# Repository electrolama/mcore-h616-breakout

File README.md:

# mcore-h616-breakout

A breakout for the [Mango Pi MCore-H616](https://mangopi.org/mcoreh616) module.

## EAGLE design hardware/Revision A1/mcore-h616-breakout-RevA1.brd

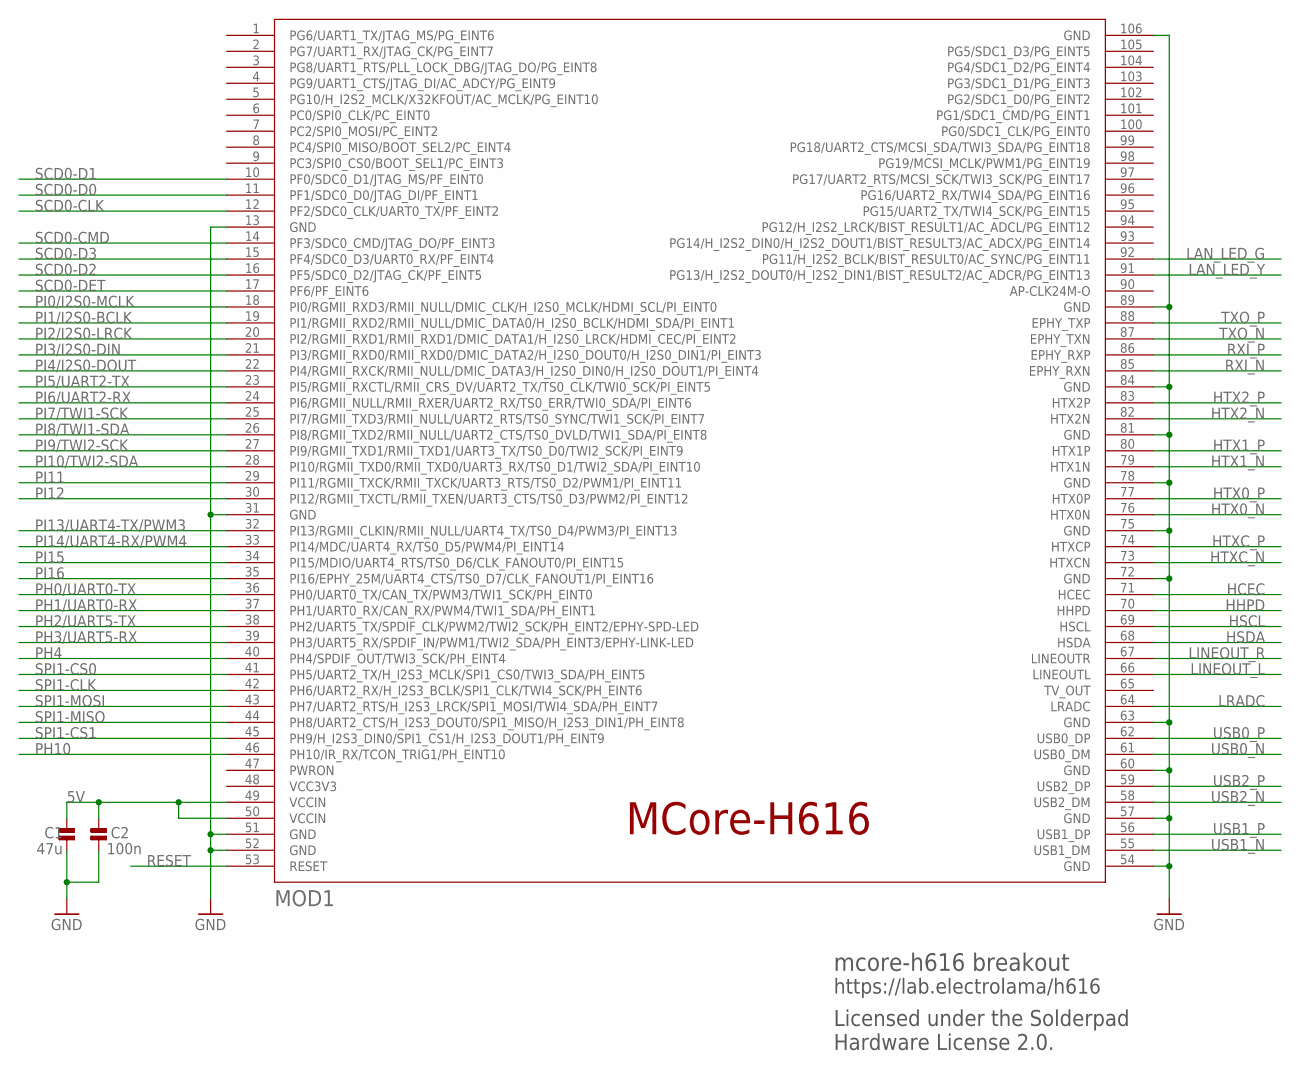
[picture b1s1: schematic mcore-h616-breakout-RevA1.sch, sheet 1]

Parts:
C1: 47u; _PKG_C_1206; JLCASSY C96123
C2: 100n; _PKG_C_0402; JLCASSY C307331
MOD1: WIDORA_MCORE-H616_V1; MCORE-H616_V1

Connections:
5V: C1.2, C2.2, MOD1.49 (VCCIN), MOD1.50 (VCCIN); also elsewhere on the board
GND: C1.1, C2.1, MOD1.13 (GND), MOD1.31 (GND), MOD1.51 (GND), MOD1.52 (GND), MOD1.54 (GND), MOD1.57 (GND), MOD1.60 (GND), MOD1.63 (GND), MOD1.72 (GND), MOD1.75 (GND), MOD1.78 (GND), MOD1.81 (GND), MOD1.84 (GND), MOD1.89 (GND), MOD1.106 (GND); also elsewhere on the board
HCEC: MOD1.71 (HCEC); also elsewhere on the board
HHPD: MOD1.70 (HHPD); also elsewhere on the board
HSCL: MOD1.69 (HSCL); also elsewhere on the board
HSDA: MOD1.68 (HSDA); also elsewhere on the board
HTX0_N: MOD1.76 (HTX0N); also elsewhere on the board
HTX0_P: MOD1.77 (HTX0P); also elsewhere on the board
HTX1_N: MOD1.79 (HTX1N); also elsewhere on the board
HTX1_P: MOD1.80 (HTX1P); also elsewhere on the board
HTX2_N: MOD1.82 (HTX2N); also elsewhere on the board
HTX2_P: MOD1.83 (HTX2P); also elsewhere on the board
HTXC_N: MOD1.73 (HTXCN); also elsewhere on the board
HTXC_P: MOD1.74 (HTXCP); also elsewhere on the board
LAN_LED_G: MOD1.92 (PG11/H_I2S2_BCLK/BIST_RESULT0/AC_SYNC/P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); also elsewhere on the board
LAN_LED_Y: MOD1.91 (PG13/H_I2S2_DOUT0/H_I2S2_DIN1/BIST_RESU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); also elsewhere on the board
LINEOUT_L: MOD1.66 (LINEOUTL); also elsewhere on the board
LINEOUT_R: MOD1.67 (LINEOUTR); also elsewhere on the board
LRADC: MOD1.64 (LRADC); also elsewhere on the board
PH0/UART0-TX: MOD1.36 (PH0/UART0_TX/CAN_TX/PWM3/TWI1_SCK/PH_EI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); also elsewhere on the board
PH1/UART0-RX: MOD1.37 (PH1/UART0_RX/CAN_RX/PWM4/TWI1_SDA/PH_EI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); also elsewhere on the board
PH2/UART5-TX: MOD1.38 (PH2/UART5_TX/SPDIF_CLK/PWM2/TWI2_SCK/PH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); also elsewhere on the board
PH3/UART5-RX: MOD1.39 (PH3/UART5_RX/SPDIF_IN/PWM1/TWI2_SDA/PH_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); also elsewhere on the board
PH4: MOD1.40 (PH4/SPDIF_OUT/TWI3_SCK/PH_EINT4); also elsewhere on the board
PH10: MOD1.46 (PH10/IR_RX/TCON_TRIG1/PH_EINT10); also elsewhere on the board
PI0/I2S0-MCLK: MOD1.18 (PI0/RGMII_RXD3/RMII_NULL/DMIC_CLK/H_I2S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); also elsewhere on the board
PI1/I2S0-BCLK: MOD1.19 (PI1/RGMII_RXD2/RMII_NULL/DMIC_DATA0/H_I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); also elsewhere on the board
PI2/I2S0-LRCK: MOD1.20 (PI2/RGMII_RXD1/RMII_RXD1/DMIC_DATA1/H_I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); also elsewhere on the board
PI3/I2S0-DIN: MOD1.21 (PI3/RGMII_RXD0/RMII_RXD0/DMIC_DATA2/H_I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); also elsewhere on the board
PI4/I2S0-DOUT: MOD1.22 (PI4/RGMII_RXCK/RMII_NULL/DMIC_DATA3/H_I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); also elsewhere on the board
PI5/UART2-TX: MOD1.23 (PI5/RGMII_RXCTL/RMII_CRS_DV/UART2_TX/TS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); also elsewhere on the board
PI6/UART2-RX: MOD1.24 (PI6/RGMII_NULL/RMII_RXER/UART2_RX/TS0_E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); also elsewhere on the board
PI7/TWI1-SCK: MOD1.25 (PI7/RGMII_TXD3/RMII_NULL/UART2_RTS/TS0_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); also elsewhere on the board
PI8/TWI1-SDA: MOD1.26 (PI8/RGMII_TXD2/RMII_NULL/UART2_CTS/TS0_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); also elsewhere on the board
PI9/TWI2-SCK: MOD1.27 (PI9/RGMII_TXD1/RMII_TXD1/UART3_TX/TS0_D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); also elsewhere on the board
PI10/TWI2-SDA: MOD1.28 (PI10/RGMII_TXD0/RMII_TXD0/UART3_RX/TS0_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); also elsewhere on the board
PI11: MOD1.29 (PI11/RGMII_TXCK/RMII_TXCK/UART3_RTS/TS0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); also elsewhere on the board
PI12: MOD1.30 (PI12/RGMII_TXCTL/RMII_TXEN/UART3_CTS/TS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); also elsewhere on the board
PI13/UART4-TX/PWM3: MOD1.32 (PI13/RGMII_CLKIN/RMII_NULL/UART4_TX/TS0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); also elsewhere on the board
PI14/UART4-RX/PWM4: MOD1.33 (PI14/MDC/UART4_RX/TS0_D5/PWM4/PI_EINT14); also elsewhere on the board
PI15: MOD1.34 (PI15/MDIO/UART4_RTS/TS0_D6/CLK_FANOUT0/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); also elsewhere on the board
PI16: MOD1.35 (PI16/EPHY_25M/UART4_CTS/TS0_D7/CLK_FANO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); also elsewhere on the board
RESET: MOD1.53 (RESET); also elsewhere on the board
RXI_N: MOD1.85 (EPHY_RXN); also elsewhere on the board
RXI_P: MOD1.86 (EPHY_RXP); also elsewhere on the board
SCD0-CLK: MOD1.12 (PF2/SDC0_CLK/UART0_TX/PF_EINT2); also elsewhere on the board
SCD0-CMD: MOD1.14 (PF3/SDC0_CMD/JTAG_DO/PF_EINT3); also elsewhere on the board
SCD0-D0: MOD1.11 (PF1/SDC0_D0/JTAG_DI/PF_EINT1); also elsewhere on the board
SCD0-D1: MOD1.10 (PF0/SDC0_D1/JTAG_MS/PF_EINT0); also elsewhere on the board
SCD0-D2: MOD1.16 (PF5/SDC0_D2/JTAG_CK/PF_EINT5); also elsewhere on the board
SCD0-D3: MOD1.15 (PF4/SDC0_D3/UART0_RX/PF_EINT4); also elsewhere on the board
SCD0-DET: MOD1.17 (PF6/PF_EINT6); also elsewhere on the board
SPI1-CLK: MOD1.42 (PH6/UART2_RX/H_I2S3_BCLK/SPI1_CLK/TWI4_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); also elsewhere on the board
SPI1-CS0: MOD1.41 (PH5/UART2_TX/H_I2S3_MCLK/SPI1_CS0/TWI3_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); also elsewhere on the board
SPI1-CS1: MOD1.45 (PH9/H_I2S3_DIN0/SPI1_CS1/H_I2S3_DOUT1/P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); also elsewhere on the board
SPI1-MISO: MOD1.44 (PH8/UART2_CTS/H_I2S3_DOUT0/SPI1_MISO/H_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); also elsewhere on the board
SPI1-MOSI: MOD1.43 (PH7/UART2_RTS/H_I2S3_LRCK/SPI1_MOSI/TWI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); also elsewhere on the board
TXO_N: MOD1.87 (EPHY_TXN); also elsewhere on the board
TXO_P: MOD1.88 (EPHY_TXP); also elsewhere on the board
USB0_N: MOD1.61 (USB0_DM); also elsewhere on the board
USB0_P: MOD1.62 (USB0_DP); also elsewhere on the board
USB1_N: MOD1.55 (USB1_DM); also elsewhere on the board
USB1_P: MOD1.56 (USB1_DP); also elsewhere on the board
USB2_N: MOD1.58 (USB2_DM); also elsewhere on the board
USB2_P: MOD1.59 (USB2_DP); also elsewhere on the board

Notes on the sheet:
mcore-h616 breakout
https://lab.electrolama/h616
Licensed under the Solderpad Hardware License 2.0.

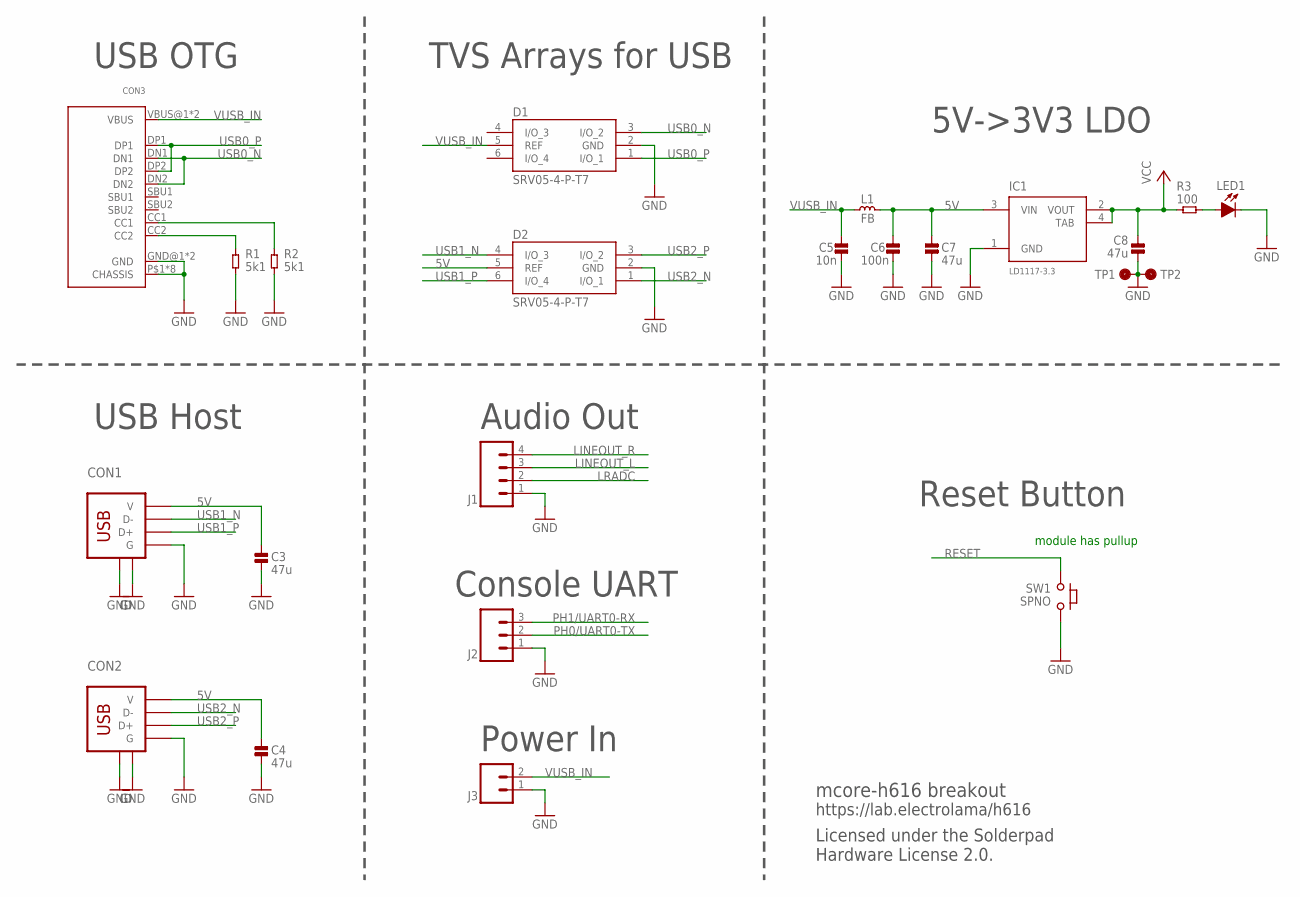
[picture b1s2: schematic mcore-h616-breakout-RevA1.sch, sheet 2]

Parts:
C3, C4, C7, C8: 47u; _PKG_C_1206; JLCASSY C96123
C5: 10n; _PKG_C_0402; JLCASSY C15195
C6: 100n; _PKG_C_0402; JLCASSY C307331
CON1, CON2: USB-A-FEMALE-JING-912-121A2023S10100; JING_912-121A2023S10100; JLCASSY C42428
CON3: USBC_USB-C-12; USBC_C-31-M-12; JLCASSY C165948
D1, D2: SRV05-4-P-T7; SOT95P280X145-6N; JLCASSY C85364
IC1: LD1117-3.3; _PKG_SOT223-4_TI-DCY4; JLCASSY C6186
J1: CONN_04LOCK; 1X04_LOCK
J2: CONN_03LOCK; 1X03_LOCK
J3: CONN_02LOCK; 1X02_LOCK
L1: FB; _PKG_C_0805; JLCASSY C75661
LED1: LED-0805; _PKG_LED_0805; JLCASSY C2296
R1, R2: 5k1; _PKG_R_0402; JLCASSY C25905
R3: 100; _PKG_R_0402; JLCASSY C25076
SW1: SPNO; GENERIC_SPNO_4P_6X6MM; JLCASSY C620316
TP1, TP2: TP; TP_DOT_1.5X1.5MM

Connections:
5V: C3.2, C4.2, C6.2, C7.2, CON1.VBUS (V), CON2.VBUS (V), D2.5 (REF), IC1.3 (VIN), L1.2; also elsewhere on the board
GND: C3.1, C4.1, C5.1, C6.1, C7.1, C8.1, CON1.GND (G), CON1.P$5 (SHIELD1), CON1.P$6 (SHIELD2), CON2.GND (G), CON2.P$5 (SHIELD1), CON2.P$6 (SHIELD2), CON3.GND@1 (GND), CON3.GND@2 (GND), CON3.P$1 (CHASSIS), CON3.P$2 (CHASSIS), CON3.P$3 (CHASSIS), CON3.P$4 (CHASSIS), CON3.P$5 (CHASSIS), CON3.P$6 (CHASSIS), CON3.P$7 (CHASSIS), CON3.P$8 (CHASSIS), D1.2 (GND), D2.2 (GND), IC1.1 (GND), J1.1, J2.1, J3.1, LED1.C, R1.1, R2.1, SW1.P$3 (2), SW1.P$4 (2), TP1.TP, TP2.TP; also elsewhere on the board
LINEOUT_L: J1.3; also elsewhere on the board
LINEOUT_R: J1.4; also elsewhere on the board
LRADC: J1.2; also elsewhere on the board
unnamed: LED1.A, R3.1
unnamed: CON3.CC1, R2.2
unnamed: CON3.CC2, R1.2
PH0/UART0-TX: J2.2; also elsewhere on the board
PH1/UART0-RX: J2.3; also elsewhere on the board
RESET: SW1.P$1 (1), SW1.P$2 (1); also elsewhere on the board
USB0_N: CON3.DN1, CON3.DN2, D1.3 (I/O_2); also elsewhere on the board
USB0_P: CON3.DP1, CON3.DP2, D1.1 (I/O_1); also elsewhere on the board
USB1_N: CON1.DM (D-), D2.4 (I/O_3); also elsewhere on the board
USB1_P: CON1.DP (D+), D2.6 (I/O_4); also elsewhere on the board
USB2_N: CON2.DM (D-), D2.1 (I/O_1); also elsewhere on the board
USB2_P: CON2.DP (D+), D2.3 (I/O_2); also elsewhere on the board
VCC: C8.2, IC1.2 (VOUT), IC1.4 (TAB), R3.2; also elsewhere on the board
VUSB_IN: C5.2, CON3.VBUS@1 (VBUS), CON3.VBUS@2 (VBUS), D1.5 (REF), J3.2, L1.1

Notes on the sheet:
module has pullup
USB OTG
TVS Arrays for USB
USB Host
Audio Out
Console UART
Power In
Reset Button
5V->3V3 LDO
mcore-h616 breakout
https://lab.electrolama/h616
Licensed under the Solderpad Hardware License 2.0.

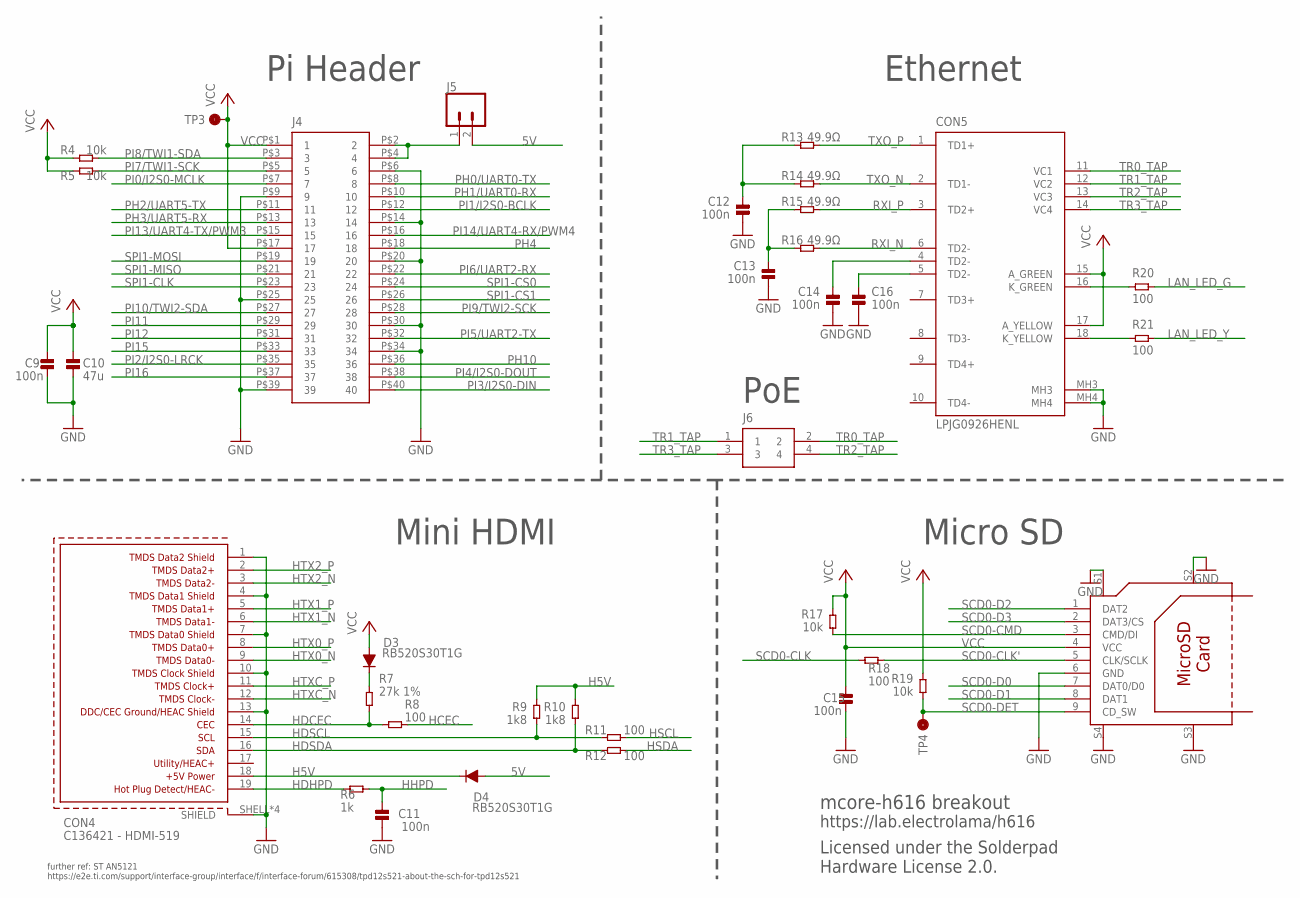
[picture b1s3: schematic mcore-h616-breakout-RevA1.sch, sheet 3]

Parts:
C9, C11, C12, C13, C14, C15, C16: 100n; _PKG_C_0402; JLCASSY C307331
C10: 47u; _PKG_C_1206; JLCASSY C96123
CON4: C136421 - HDMI-519; 685119136923; JLCASSY C136421
CON5: LPJG0926HENL
CON6: C111196 - TF-15x15; TF/SHENZHEN-SPECIAL; JLCASSY C111196
D3, D4: RB520S30T1G; _PKG_SOD523; JLCASSY C154821
J4: CON_2.54MM_TH_2X20
J5: CONN_02LOCK; 1X02_LOCK
J6: CON_2.54MM_TH_2X2
R4, R5, R17, R19: 10k; _PKG_R_0402; JLCASSY C25744
R6: 1k; _PKG_R_0402; JLCASSY C11702
R7: 27k 1%; _PKG_R_0402; JLCASSY C25771
R8, R11, R12, R18, R20, R21: 100; _PKG_R_0402; JLCASSY C25076
R9, R10: 1k8; _PKG_R_0402; JLCASSY C25871
R13, R14, R15, R16: 49.9Ω; _PKG_R_0402; JLCASSY C25120
TP3, TP4: TP; TP_DOT_1.5X1.5MM

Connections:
5V: D4.2 (A), J5.2; also elsewhere on the board
GND: C9.1, C10.1, C11.1, C12.1, C13.1, C14.1, C15.1, C16.1, CON4.1 (TMDSDATA2SHIELD), CON4.4 (TMDSDATA1SHIELD), CON4.7 (TMDSDATA0SHIELD), CON4.10 (TMDSCLOCKSHIELD), CON4.13 (DDC/CECGROUND/HEACSHIELD), CON4.SHELL (SHIELD), CON4.SHELL1 (SHIELD), CON4.SHELL2 (SHIELD), CON4.SHELL3 (SHIELD), CON5.MH3, CON5.MH4, CON6.6 (GND), CON6.S1, CON6.S2, CON6.S3, CON6.S4, J4.P$6 (6), J4.P$9 (9), J4.P$14 (14), J4.P$20 (20), J4.P$25 (25), J4.P$30 (30), J4.P$34 (34), J4.P$39 (39); also elsewhere on the board
H5V: CON4.18 (+5VPOWER), D4.1 (C), R9.1, R10.1
HCEC: R8.2; also elsewhere on the board
HDCEC: CON4.14 (CEC), R7.1, R8.1
HDHPD: CON4.19 (HOTPLUGDETECT/HEAC-), R6.1
HDSCL: CON4.15 (SCL), R9.2, R11.1
HDSDA: CON4.16 (SDA), R10.2, R12.1
HHPD: C11.2, R6.2; also elsewhere on the board
HSCL: R11.2; also elsewhere on the board
HSDA: R12.2; also elsewhere on the board
HTX0_N: CON4.9 (TMDSDATA0-); also elsewhere on the board
HTX0_P: CON4.8 (TMDSDATA0+); also elsewhere on the board
HTX1_N: CON4.6 (TMDSDATA1-); also elsewhere on the board
HTX1_P: CON4.5 (TMDSDATA1+); also elsewhere on the board
HTX2_N: CON4.3 (TMDSDATA2-); also elsewhere on the board
HTX2_P: CON4.2 (TMDSDATA2+); also elsewhere on the board
HTXC_N: CON4.12 (TMDSCLOCK-); also elsewhere on the board
HTXC_P: CON4.11 (TMDSCLOCK+); also elsewhere on the board
LAN_LED_G: R20.2; also elsewhere on the board
LAN_LED_Y: R21.2; also elsewhere on the board
unnamed: CON5.16 (K_GREEN), R20.1
unnamed: C14.2, CON5.4 (TD2-)
unnamed: C16.2, CON5.5 (TD2-)
unnamed: J4.P$2 (2), J4.P$4 (4), J5.1
unnamed: CON5.18 (K_YELLOW), R21.1
unnamed: D3.1 (C), R7.2
unnamed: C12.2, R13.1, R14.1
unnamed: C13.2, R15.1, R16.1
PH0/UART0-TX: J4.P$8 (8); also elsewhere on the board
PH1/UART0-RX: J4.P$10 (10); also elsewhere on the board
PH2/UART5-TX: J4.P$11 (11); also elsewhere on the board
PH3/UART5-RX: J4.P$13 (13); also elsewhere on the board
PH4: J4.P$18 (18); also elsewhere on the board
PH10: J4.P$36 (36); also elsewhere on the board
PI0/I2S0-MCLK: J4.P$7 (7); also elsewhere on the board
PI1/I2S0-BCLK: J4.P$12 (12); also elsewhere on the board
PI2/I2S0-LRCK: J4.P$35 (35); also elsewhere on the board
PI3/I2S0-DIN: J4.P$40 (40); also elsewhere on the board
PI4/I2S0-DOUT: J4.P$38 (38); also elsewhere on the board
PI5/UART2-TX: J4.P$32 (32); also elsewhere on the board
PI6/UART2-RX: J4.P$22 (22); also elsewhere on the board
PI7/TWI1-SCK: J4.P$5 (5), R5.2; also elsewhere on the board
PI8/TWI1-SDA: J4.P$3 (3), R4.2; also elsewhere on the board
PI9/TWI2-SCK: J4.P$28 (28); also elsewhere on the board
PI10/TWI2-SDA: J4.P$27 (27); also elsewhere on the board
PI11: J4.P$29 (29); also elsewhere on the board
PI12: J4.P$31 (31); also elsewhere on the board
PI13/UART4-TX/PWM3: J4.P$15 (15); also elsewhere on the board
PI14/UART4-RX/PWM4: J4.P$16 (16); also elsewhere on the board
PI15: J4.P$33 (33); also elsewhere on the board
PI16: J4.P$37 (37); also elsewhere on the board
RXI_N: CON5.6 (TD2-), R16.2; also elsewhere on the board
RXI_P: CON5.3 (TD2+), R15.2; also elsewhere on the board
SCD0-CLK: R18.2; also elsewhere on the board
SCD0-CLK': CON6.5 (CLK/SCLK), R18.1
SCD0-CMD: CON6.3 (CMD/DI), R17.1; also elsewhere on the board
SCD0-D0: CON6.7 (DAT0/D0); also elsewhere on the board
SCD0-D1: CON6.8 (DAT1); also elsewhere on the board
SCD0-D2: CON6.1 (DAT2); also elsewhere on the board
SCD0-D3: CON6.2 (DAT3/CS); also elsewhere on the board
SCD0-DET: CON6.9 (CD_SW), R19.1, TP4.TP; also elsewhere on the board
SPI1-CLK: J4.P$23 (23); also elsewhere on the board
SPI1-CS0: J4.P$24 (24); also elsewhere on the board
SPI1-CS1: J4.P$26 (26); also elsewhere on the board
SPI1-MISO: J4.P$21 (21); also elsewhere on the board
SPI1-MOSI: J4.P$19 (19); also elsewhere on the board
TR0_TAP: CON5.11 (VC1), J6.2
TR1_TAP: CON5.12 (VC2), J6.1
TR2_TAP: CON5.13 (VC3), J6.4
TR3_TAP: CON5.14 (VC4), J6.3
TXO_N: CON5.2 (TD1-), R14.2; also elsewhere on the board
TXO_P: CON5.1 (TD1+), R13.2; also elsewhere on the board
VCC: C9.2, C10.2, C15.2, CON5.15 (A_GREEN), CON5.17 (A_YELLOW), CON6.4 (VCC), D3.2 (A), J4.P$1 (1), J4.P$17 (17), R4.1, R5.1, R17.2, R19.2, TP3.TP; also elsewhere on the board

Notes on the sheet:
Mini HDMI
Pi Header
Ethernet
PoE
Micro SD
mcore-h616 breakout
https://lab.electrolama/h616
Licensed under the Solderpad Hardware License 2.0.
further ref: ST AN5121 https://e2e.ti.com/support/interface-group/interface/f/interface-forum/615308/tpd12s521-about-the-sch-for-tpd12s521

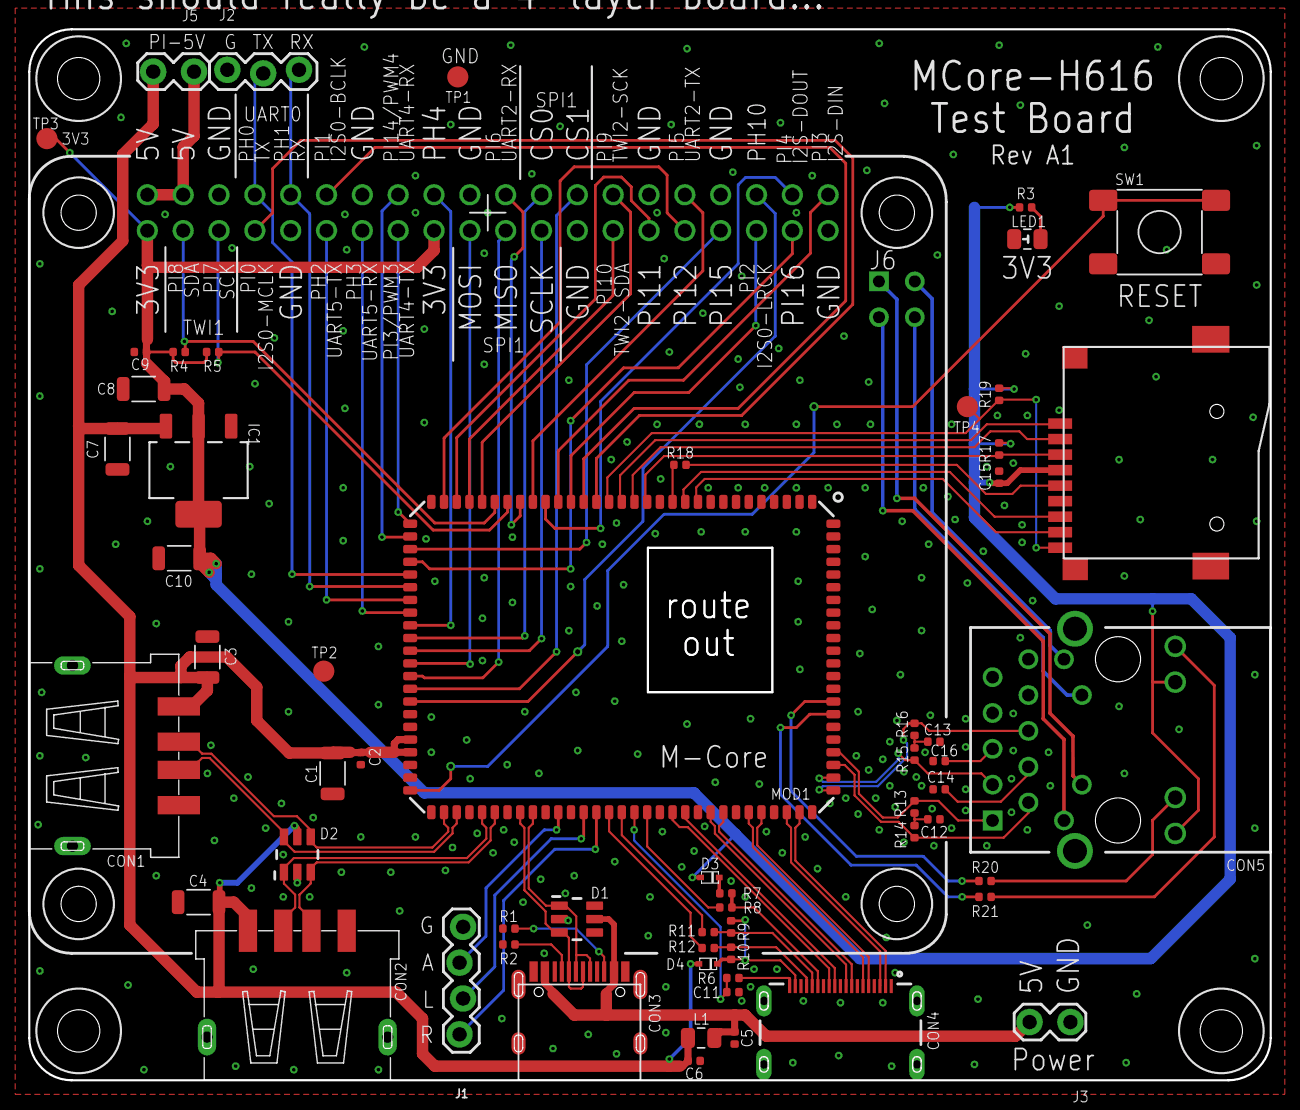
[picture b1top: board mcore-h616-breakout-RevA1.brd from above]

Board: 2 copper layers, 88.0 x 74.5 mm, 62 parts (0 on the bottom side), 88 nets.

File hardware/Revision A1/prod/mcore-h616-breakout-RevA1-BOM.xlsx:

Comment | Designator | Footprint | JLCPCB Part # | Manufacturer | MPN | Qty
 | J3, J5 | 1X02_LOCK |  |  |  | 2
 | J2 | 1X03_LOCK |  |  |  | 1
 | J1 | 1X04_LOCK |  |  |  | 1
 | J6 | CON_2.54MM_TH_2X2 |  |  |  | 1
 | J4 | CON_2.54MM_TH_2X20 |  |  |  | 1
 | LED1 | _PKG_LED_0805 | C2296 |  |  | 1
 | CON1, CON2 | JING_912-121A2023S10100 | C42428 |  |  | 2
 | CON3 | USBC_C-31-M-12 | C165948 |  |  | 1
 | MOD1 | MCORE-H616_V1 |  |  |  | 1
100 | R3, R8, R11, R12, R18, R20, R21 | _PKG_R_0402 | C25076 |  |  | 7
100n | C2, C6, C9, C11, C12, C13, C14, C15, C16 | _PKG_C_0402 | C307331 |  |  | 9
10k | R4, R5, R17, R19 | _PKG_R_0402 | C25744 |  |  | 4
10n | C5 | _PKG_C_0402 | C15195 |  |  | 1
1k | R6 | _PKG_R_0402 | C11702 |  |  | 1
1k8 | R9, R10 | _PKG_R_0402 | C25871 |  |  | 2
27k 1% | R7 | _PKG_R_0402 | C25771 |  |  | 1
47u | C1, C3, C4, C7, C8, C10 | _PKG_C_1206 | C96123 |  |  | 6
49.9Ω | R13, R14, R15, R16 | _PKG_R_0402 | C25120 |  |  | 4
5k1 | R1, R2 | _PKG_R_0402 | C25905 |  |  | 2
C111196 - TF-15x15 | CON6 | TF/SHENZHEN-SPECIAL | C111196 |  |  | 1
C136421 - HDMI-519 | CON4 | 685119136923 | C136421 |  |  | 1
FB | L1 | _PKG_C_0805 | C75661 |  |  | 1
LD1117-3.3 | IC1 | _PKG_SOT223-4_TI-DCY4 | C6186 |  |  | 1
LPJG0926HENL | CON5 | LPJG0926HENL |  |  |  | 1
RB520S30T1G | D3, D4 | _PKG_SOD523 | C154821 |  |  | 2
SPNO | SW1 | GENERIC_SPNO_4P_6X6MM | C620316 |  |  | 1
SRV05-4-P-T7 | D1, D2 | SOT95P280X145-6N | C85364 |  |  | 2

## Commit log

2022-08-01 initial check-in for RevA1
2022-08-01 add reference material
2022-08-04 clean-up and mfg release for rev A1
2022-08-04 proper pdf export of schematics
2022-12-14 add refs
2022-12-14 add photo of assembled boards

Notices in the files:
parts and their libraries:
Wurth_Connectors_WR-HDMI: Copyright: Würth Elektronik
SparkFun-Connectors: Licensing: Creative Commons ShareAlike 4.0 International - https://creativecommons.org/licenses/by-sa/4.0
